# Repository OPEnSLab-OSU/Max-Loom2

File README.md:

# Max Documentation

## Purpose

* Designed to interface with the Loom Internet of Things Rapid Prototyping framework ([GitHub - OPEnSLab-OSU/Loom: Arduino library for Internet of Things Rapid Prototyping in environmental sensing](https://github.com/OPEnSLab-OSU/Loom))
* Uses software Max: [What is Max? | Cycling ’74](https://cycling74.com/products/max)
	* Tool for creating interactive software

### This Readme
* Designed to cover the usage of Max for interfacing with Loom, as well as some details of how it is implemented
	* It is not designed to be a readme of how to modify / create new patches or functionality

### Where to Put these Files
* Place this folder into the following directory:
  * If using Max 7 or 8:
    * [user] / Documents / Max 7 / Library
  * If using Max 6:
    * [user] / Applications / Max6 / Cycling74 

*Note: most of these the Max Loom files are developed in Max 8, functionality outside of this version may vary*

### Developer notes:
* These files should be in the same folder
* Some functionality (e.g. UDP communication) will only work on Max 8
* The Z_ patches may not work or depend on non-default features in Max 8

- - - -

# Installation Guide
## Download Max:
Go to Cycling 74 and download the version for your operating system.

Open Max 8 Application so the support folders you need to place the support files generate in your Documents folder.

You may want to create an account for authorization

## Download Loom Tools for Max:
* Go to: [https://github.com/OPEnSLab-OSU/Max-Loom2](https://github.com/OPEnSLab-OSU/Max-Loom2)
* Click the green button on the right to download the .zip of the repo.
* Unzip

Find these three folders:
* Loom2
* MPG
* Optron

Drag these folders into the following folder on your computer: 

(User) > Documents > Max 8 > Library 

## Download Java:
Make sure java is installed, especially if you are a windows user. 

Install Java here. [Java](https://www.java.com/en/download/manual.jsp)

## Download Java Virtual Machine (JDK):
Even if you installed Java above, you still need to do the following:
In a google search, type in: "download oracle java"
Click Java SE Downloads
Look for Oracle JDK and click the JDK download link 
Choose the operating system that matches your computer and download.
[Direct Link](https://www.oracle.com/java/technologies/javase-jdk14-downloads.html)

## Download the FTDI VCP drivers (virtual com port)
[ftdichip.com/drivers/vcp.htm](ftdichip.com/drivers/vcp.htm)

Don't download the D2xx drivers.
You only need to download the VCP drivers.
(make sure to download the executable version for your opperating system)

## Download Link Tools:
* From the Max 8 application, look for the menu item > Package manager
* Top right corner, type “link” in the search bar
* Install Link by Cycling ‘74

## reStart and reOpen Max 8:
* Quit Max, you may need to restart your computer too.
* Reopen Max8

## Try Things Out:
On your computer, Open (User) > Documents > Max 8 > Library > Loom2 > _DataProcessor.MPG.maxpat

- - - -

# Patches

* Patches are self-contained blocks with inputs and outputs for commands / data
* Inlets are the little circles at the top of a patch, hovering over them will give a description
* Outlets are the little circles at the bottom of a patch, hovering over them will give a description

## General

#### ModuleCore (primary input from Loom device)
##### Description

* Can think of as a representation a Loom device (device running Loom software, and enabled with Max interfacing features)
* A number of the patches are intended to be parallels to individual features / components enabled in the config of the Loom device

##### UI Elements

* `Instance number`: Enter the device number to connect to (specified in the config file)
* `Data updating`: When data is being received, this indicator blinks when data is being received (updates at 500ms interval if data is being received faster than that)
* `Battery indicator`: Display the battery level of the connected Loom device
* `Device name`: The name of the Loom device as specified in the config file
* `Send IP button`: Press to send the IP of the computer running Max to the Loom device. The device will save this and send data to specifically that IP rather than broadcasting data (increases data reliability)

##### Inlets

1. `Device ID In`: change the device to connect to
2. `JS Commands In`: Commands from actuator patches to converted to format and send to the Loom device
3. `Bang to Send IP`: Input bang signal to send IP to Loom device

##### Outlets

1. `Json Out`: Received data in Json format
2. `Data Dictionary Out`: Received data in Max dictionary format

- - - -

## Displays

### GeneralViewer
##### Description

* Accepts data as either a Json object or a Max Dictionary and displays is for easier viewing

##### UI Elements

* Large area to display data
* ‘Freeze’ button to prevent new data from overwriting currently displayed data

##### Inlets

1. `Data (Json) In`: Data in Json format (works with non-Loom data)
2. `Data (Dict) In`: Data in Max dictionary format (works with non-Loom data)

##### Outlets

1. None

### Sensor
##### Description

* Displays data from Loom devices 
* Intended to be connected to ’Json Out’ outlet of a ‘ModuleCore’

##### UI Elements

* Drop down of which sensor to display data for (items correspond to Loom Modules)
* Drop down of which element to display for the selected sensor / module
* Last reported value
* Moving average histogram of recent values

##### Inlets

1. `Data (Json) In`

##### Outlets

1. Outgoing data of current parameter 

##### Notes

* Data parsing and UI updating is primarily done via Sensor.js script

### PositionVisualizer
##### Description

* Displays the 3D orientation of Loom device with MPU6050
* Intended to be connected to ’Json Out’ or ‘Data Dictionary Out’ outlet of a ‘ModuleCore’

##### UI Elements

* Orientation visualization

##### Inlets

1. `Data (Json) In`: Loom data from ModuleCore
2. `Data (Dict) In`: Loom data from ModuleCore

##### Outlets

1. Output

- - - -

## Outputs (to network)

### Neopixel
##### Description

* Set the color of a Neopixel connected to a Loom device (generally connected to an Ishield)
* Corresponds to Loom ‘Neopixel’ module

##### UI Elements

* ‘Send’ button: generate command
* Dropdown menu to select which port the Neopixel / Neopixel chain is connected to 
* Dropdown menu to select which Neopixel to set in an a chain
* Sliders to select red, green, and blue values (0-255)

##### Inlets

1. `Bang to Send`: generate command upon bang 
2. `Reset to Defaults`
3. `Port Number`
4. `Neopixel # In Chain`
5. `Red Value (0-255)`
6. `Green Value (0-255)`
7. `Blue Value (0-255)`

##### Outlets

1. `JS Command Out`: Intended to be connected ‘JS Commands In’ outlet of ‘ModuleCore’

### Relay
##### Description

* Set the state of a relay connected to a Loom device
* Corresponds to Loom `Relay` module

##### UI Elements

* ‘Send’ button: generate command
* Button toggle to set relay state (green: enabled, gray: off)
* ‘Auto Send’ toggle: (enabled: changing main toggle immediately generates command: disabled: commands only generated when ‘Send’ button is pressed

##### Inlets

1. `Bang to Send`: generate command upon bang 
2. `Set State (1 on, 0 off)`

##### Outlets

1. `JS Command Out`: Intended to be connected ‘JS Commands In’ outlet of ‘ModuleCore’

### Servo
##### Description

* Set the position of a servo connected to a Loom device
* Corresponds to Loom ‘Servo’ module

##### UI Elements

* ‘Send’ button: generate command
* Dropdown to select which servo to set

##### Inlets

1. `Bang to Send`: generate command upon bang 
2. `Reset to Defaults`
3. `Servo Number` 
4. `Degree`

##### Outlets

1. `JS Command Out`: Intended to be connected ‘JS Commands In’ outlet of ‘ModuleCore’

### Stepper
##### Description

* Control rotation of stepper connect to Loom device
* Corresponds to Loom ‘Servo’ module

##### UI Elements

* ‘Send’ button: generate command
* Dropdown to select which motor to control
* Number of steps to move input 
* Speed entry: 10-250

##### Inlets

1. `Bang to Send`: generate command upon bang 
2. `Reset to Defaults` 
3. `Motor #`
4. `Set Speed`
5. `Clockwise`

##### Outlets

1. `JS Command Out`: Intended to be connected ‘JS Commands In’ outlet of ‘ModuleCore’

### SetInterval
##### Description

* Set the refresh rate of a Loom device

##### UI Elements

* ‘Send’ button: generate command

##### Inlets

1. `Bang to Send`: generate command upon bang 
2. `Interval (ms)`: refresh rate of Loom devices

##### Outlets

1. `JS Command Out`: Intended to be connected ‘JS Commands In’ outlet of ‘ModuleCore’

#### SelectSD_Config
##### Description

* Specify a config file for a Loom device to reinitialize with
* Requires that the Loom device be connected to an SD card

##### UI Elements

* Dropdown to select Loom config file (names populated from items in ‘SD_Json_Menu.txt’
  * Populate .txt file with common config names
* Text box to manually enter Loom config file name

##### Inlets

1. `Bang to Send`: generate command upon bang 
2. `Reset to Defaults`

##### Outlets

1. `JS Command Out`: Intended to be connected ‘JS Commands In’ outlet of ‘ModuleCore’

- - - -

## Middleware Patches 
*Used for transforming values / data streams*

### Aux_RangeSetter
##### Description
  * Scales an input stream of values to fit within the specified ‘Min’ and ‘Max’ values
  * Intended that the ‘Learn’ toggle be active while adjusting the input (output from a Loom device or otherwise) between its maximum ranges, then deactivating ‘Learn’
    * Subsequent values will use the detected min and max values of the input and map them to the output min and max values, with other values being interpolated within the range
    * Incoming values outside of the learned min and max while ‘Learn’ is disabled will be capped within the range
  * Rescales an incoming data stream of an unknown range into a stream with a specified minimum and maximum range. Range Setter automatically adjusts and compares incoming values based on the least and greatest values it received while in "Learn" mode. 

##### UI Elements
  * Output ‘Min’ and ‘Max’ range
* ‘Learn’ toggle: enable and send your min and max value. Then disable to save min/max and disable Learn mode.
* Mapped value of most recent input value
* History of values
* Reset button: Clear learned ranged
##### Inlets
1. `Incoming Values`: stream of values to remap
2. `Save/reset`: 1: reset learned values and enable learn mode, 0: disable learn mode, saving learned range
##### Outlets
1. `Range adjusted value`: stream of values remapped to specified range

### Aux_ScaleCurve
##### Description
  * Remap a [0, 1] data stream through a selection of functions
  * Data not in [0, 1] can be remapped to this range with ‘Rescale’ or ‘Range Setter’ patches
  * Transformation equations:
    * x is in range [0, 1] 
    * Cosine: (x–1^3) * (x+1^3) + 1
    * CrossFadeIn: sin(x * π/2)
    * Exponential: x^a
    * Linear: Simply caps input stream to [0,1) range
    * Bell: sin(x * π)
    * Gaussian: e^[–(x–0.5^2) / (2*(0.157^2)]
    * InvGauss: -e^[–(x–0.5^2) / (2*(0.157^2)] + 1
    * Inverted Ramp: cos(x * π) 
##### UI Elements
  * Dropdown to select which function to map input stream to
  * Exponent: Only applies if ‘exponential’ function is selected
  * Visualization of function and current input and output values along the curve
  * Histogram of recent values
##### Inlets
  1. `Value to Scale`: Stream of data (or single value), representing ‘x’ values to specified functions (should be in [0,1])
##### Outlets
  1. `Scaled Value`: Stream of data mapped through the specified equation

### Aux_ScaleLinear
##### Description
  * Maps a stream of data from the specified input range to the specified output range, interpolating to scale values
  * Similar to ‘Range Setter’ patch but expects know input range
##### UI Elements
  * Input Min and Max values
  * Output Min and Max values
##### Inlets
  1. `Value to Scale`: Input stream of data (or single value) to scale to a different range
##### Outlets
  1. `Scaled Value`: Stream of data remapped to specified range

### Aux_Smooth
##### Description
  * Smooths data stream logarithmically
  * Uses an averaging function to affect rising and falling in a data stream. This can have a smoothing affect on the data stream,
  * Slider values indicate how many samples to average together
  * Also note, The Smooth value is inversely correlational to the data's responsiveness. i.e. the higher the Smoothing value, the more sluggish the data will be to respond in a rising or falling direction
##### UI Elements
  * Filter strength rising: [0,21], strength of smoothing on rising data
  * Filter strength falling: [0,21], strength of smoothing on falling data
  * Histogram of recent values:
  * Most recent value
##### Inlets
  1. `Value to Smooth`: Stream of data to smooth
##### Outlets
  1. `Smoothed Value`: Stream of data smoothed 

### Aux_Threshold
##### Description
  * Output boolean values triggered when a stream of data values risings or falls past specified thresholds
##### UI Elements
  * Rising threshold: If previous value is <= this value and most recent value is >, output true
  * Falling threshold: If previous value is >= this value and most recent value is <, output false
  * Invert logic toggle: Invert the boolean output
##### Inlets
  1. Data stream to check threshold on
  2. Rising threshold: Value to use as rising threshold
  3. Falling threshold: Value to use as falling threshold
##### Outlets
  1. True of false based on logic 

### Aux_pH
##### Description
  * Used to convert raw millivolt readings of a pH probe to a pH value
  * Calibrate the sensor by getting the readings in buffers with pH of 4 and 7
##### UI Elements
  * Acid pH 4 calibration reading: millivolt reading when probe is placed in buffer with pH 4
  * Neutral pH 7 calibration reading:  millivolt reading when probe is placed in buffer with pH 7
  * Calculated pH of current mV reading
##### Inlets
  1. Current reading in (mV)
  2. pH 4 Acid mV
  3. pH 7 Neutral mV
##### Outlets
  1. pH value 

- - - -

## Other
Additional patches created before the current design of Loom. Support with Loom functionality may vary

* Z_3Dpan
* Z_App3DPan
* Z_AppVST
* Z_ArduinoIn
* Z_ChordDegree
* Z_Concatenate
* Z_DMX
* Z_Draw
* Z_DrumKit
* Z_Follower_GUI
* Z_InstrumentPosition
* Z_MidiIn
* Z_MidiOut
* Z_Movement
* Z_Musicbox
* Z_OSC_In
* Z_OSC_Out
* Z_OutLightsaber
* Z_RotaryDial
* Z_ScaleDegree
* Z_Sequencer
* Z_SimpleSamp
* Z_Spring
* Z_Switchblade
* Z_TapTempo

- - - -

## Data Processor
* Essentially a sandbox to use the other patches
* Starts out with just the ‘Patch Generator’
  * Has a dropdown of ‘patches’ that can be generated
    * Sorted in terms of inputs, outputs, data modification,  visualization
  * ‘Clear Last Patch’: deletes the most recently generated patch
  * ‘Clear All Patches’: deletes all patches 
  * Relevant files:
    * Patch_Generator.maxpat
    * PatchList.txt (kept separate so it is easy to modify list as new patches are added

### Usage
* Generate patches 
* Designed primarily to be used with Loom devices, so generating a/multiple ModuleCores will be useful
  * Once the device number is set to match the corresponding Loom device (number set in the Loom config file), data will output from the to outlets of the patch
* Attach viewers / data processing patches to the outlets 
* Attach command generating patches to inlets

* If you need to modify / inspect the internals of the patch that was generated in a DataProcessor file, you can Right Click > Object > ‘New View of Embedded Patcher’ (or ‘New Patcher with Contents of Embedded Patcher’ if you don’t want modifications to affect the DataProcessor file

* Can ‘Save As’ to create templated

- - - -

## Loom Implementation

### MaxSub
* Receives commands from Max
  * Commands can be generated from actuator patches connected to a ‘ModuleCore’ (or can be manually created strings)
* Can be run without MaxPub if you only want to receive commands and not send data, reliability may not be as good as with both modules
* Commands will be routed to ‘MaxSub’ module, which will ‘dispatch’ the command to the corresponding module’s ‘dispatch’ method to act upon it
* Needs `Loom.MaxSub().subscribe();` in the main loop
* Receives on UDP port 9000 + instance number (thus Max sends on this port)
* Requires an ‘InternetPlat’ module be instantiated
* When ‘ModuleCore’ is created / ‘Send IP’ is pressed, Max sends out the IP of the computer it is running on to the device of the specified instance number, if such a devices exists and is running ‘MaxSub’ and ‘MaxPub’ modules, the device will set that IP in the ‘MaxPub’ module to have better reliability sending messages 

### MaxPub
* Used to send data out to Max
* Can be used without MaxSub if you only want to send data, reliability may not be as good as with both modules
* Sends on UDP port 8000 + instance number (thus Max receives on this port)
* Requires an ‘InternetPlat’ module be instantiated
* Needs `Loom.MaxPub().publish();` in the main loop
  * After measuring and packaging data, this will send the data object/package out to Max

- - - -

## Max Implementation

### Loom Core
* Represents a Loom devices 
  * Outputs Loom device packaged data
  * Inputs commands to send to Loom device
* Nearly all of the logic is controlled by `Controller.js` file (the rest is essentially just the UI elements and formatting inputs to send to the Javascript object)

#### Controller.js Functions
* `json(j)`
  * Parse data the has been received via UDP in the `UDP_In` patcher (which does some initial preprocessing / filtering of non-data; see `Convert_Incoming.js` for details)
  * Calls function to update UI with new data
  * Extract the IP address of the Loom device, and respond with command to MaxPub module to have Loom device set the remote IP to be the IP of the computer running Max
  * Update the `Data` dict object
  * Forward the data json out
* `update_UI()`
  * Calls functions to update UI elements for battery, device name, blink messages received
* `update_UI_battery()`
  * Update the battery UI element (named `battery_indicator`) with the last received battery voltage
* `update_UI_device_name()`
  * Update the device name UI element (named `device_name`) with last received device name 
  * Max only specifies the device to connect to by ID number, it does not know about the name until it receives data, which is displayed for better human readability
* `update_UI_blink_received()`
  * Update the UI LED that blinks when data is received
* `enable_log(e)`
  * Enable or disable logging to the Max console
* `set_instance(i)`
  * Reset the UI of current device info
  * Set the UDP elements to receive / send on the updated ports
* `command(argSymbol)`
  * Given a symbol (string) of a command, format a message that the MaxSub module will recognize and be able to dispatch
  * Send the json command out to `UDP_Out` to be sent over UDP
* `reset_UI()`
  * Any UI clearing / resetting that needs to happen when switching devices, for example
* `set_ip()`
  * Create a command to MaxPub module to have Loom device set the remote IP to be the IP of the computer running Max
  * Send the json command out to `UDP_Out` to be sent over UDP

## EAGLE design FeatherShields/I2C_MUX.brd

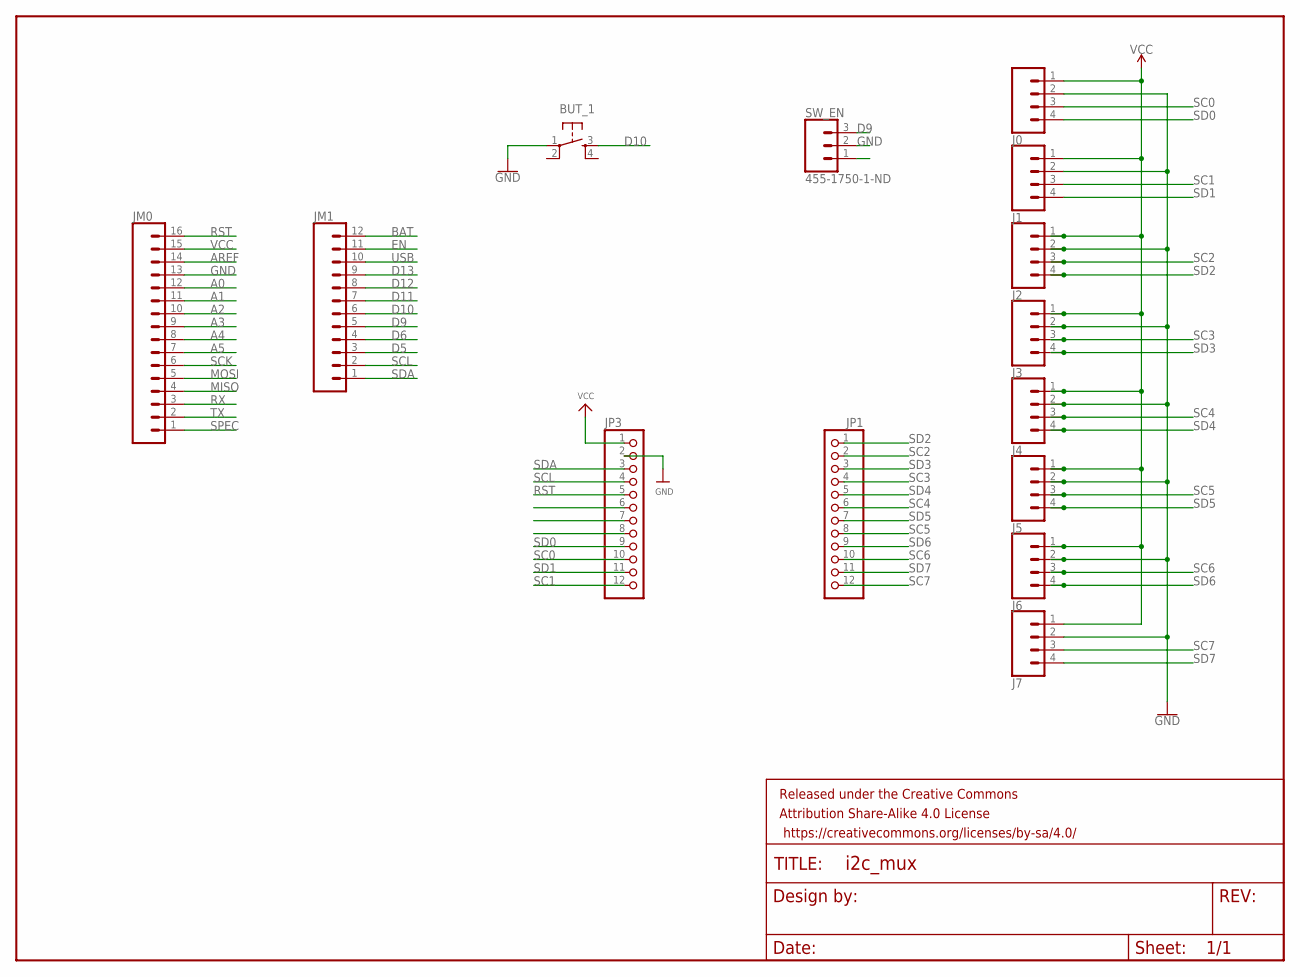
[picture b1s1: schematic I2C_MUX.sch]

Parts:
BUT_1: TAC_SWITCHPTH; TACTILE-PTH
FRAME1: FRAME-LETTER; CREATIVE_COMMONS
J0, J1, J2, J3, J4, J5, J6, J7: CONN_04POLAR; MOLEX-1X4
JM0: CONN_16; 1X16
JM1: CONN_12; 1X12
JP1, JP3: HEADER-1X12; 1X12_ROUND
SW_EN: 455-1750-1-ND; 1X03

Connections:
A0: JM0.12
A1: JM0.11
A2: JM0.10
A3: JM0.9
A4: JM0.8
A5: JM0.7
AREF: JM0.14
BAT: JM1.12
D5: JM1.3
D6: JM1.4
D9: JM1.5, SW_EN.3
D10: BUT_1.3, JM1.6
D11: JM1.7
D12: JM1.8
D13: JM1.9
EN: JM1.11
GND: BUT_1.1, J0.2, J1.2, J2.2, J3.2, J4.2, J5.2, J6.2, J7.2, JM0.13, JP3.2, SW_EN.2
MISO: JM0.4
MOSI: JM0.5
RST: JM0.16, JP3.5
RX: JM0.3
SC0: J0.3, JP3.10
SC1: J1.3, JP3.12
SC2: J2.3, JP1.2
SC3: J3.3, JP1.4
SC4: J4.3, JP1.6
SC5: J5.3, JP1.8
SC6: J6.3, JP1.10
SC7: J7.3, JP1.12
SCK: JM0.6
SCL: JM1.2, JP3.4
SD0: J0.4, JP3.9
SD1: J1.4, JP3.11
SD2: J2.4, JP1.1
SD3: J3.4, JP1.3
SD4: J4.4, JP1.5
SD5: J5.4, JP1.7
SD6: J6.4, JP1.9
SD7: J7.4, JP1.11
SDA: JM1.1, JP3.3
SPEC: JM0.1
TX: JM0.2
USB: JM1.10
VCC: J0.1, J1.1, J2.1, J3.1, J4.1, J5.1, J6.1, J7.1, JM0.15, JP3.1

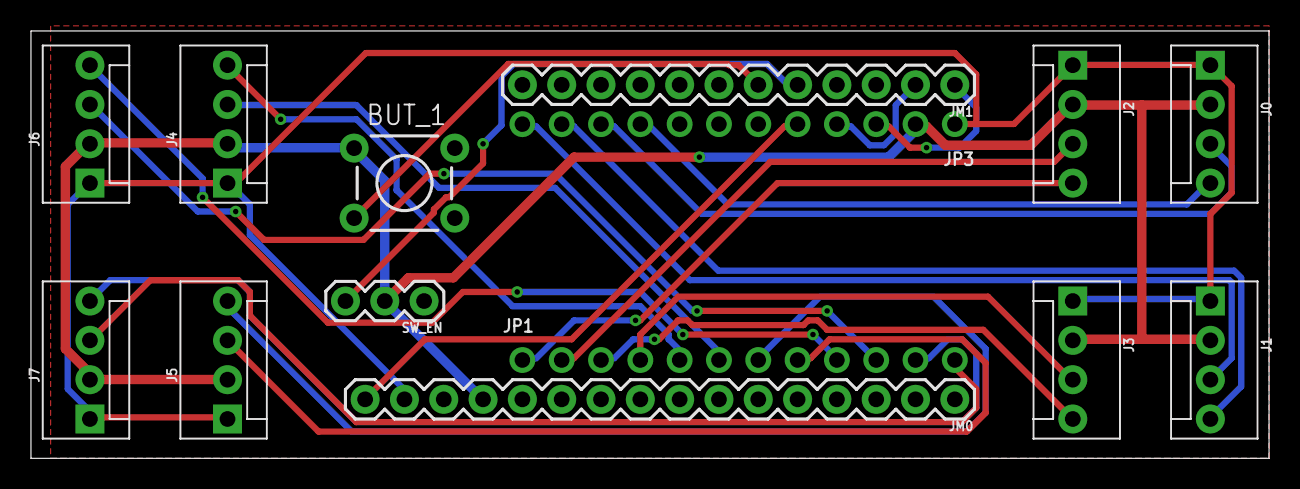
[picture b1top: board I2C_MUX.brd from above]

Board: 2 copper layers, 80.0 x 27.6 mm, 15 parts (0 on the bottom side), 23 nets.

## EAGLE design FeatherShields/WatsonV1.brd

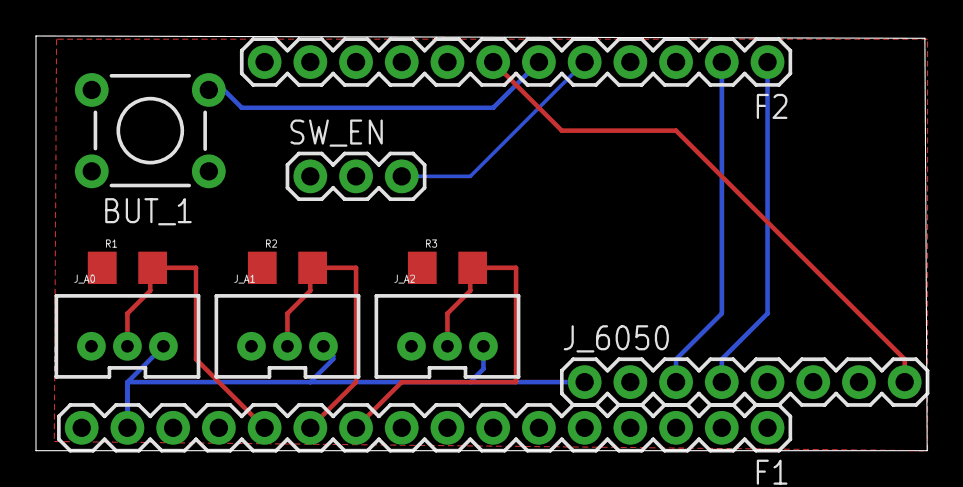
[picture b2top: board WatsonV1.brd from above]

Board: 2 copper layers, 49.5 x 23.0 mm, 11 parts (0 on the bottom side), 10 nets.

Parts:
BUT_1: TACTILE-PTH
F1: 1X16
F2: 1X12
J_6050: 1X08_ROUND
J_A0, J_A1, J_A2: JST-3-PTH-VERT
R1, R2, R3: 30k 63mW; 1206
SW_EN: 1X03

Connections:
A0: F1.12, J_A0.2, R1.2
A1: F1.11, J_A1.2, R2.2
A2: F1.10, J_A2.2, R3.2
BUTT: BUT_1.3, F2.6
GND: BUT_1.1, F1.13, J_6050.2, J_A0.1, J_A1.1, J_A2.1, R1.1, R2.1, R3.1, SW_EN.2
MPU_INT: F2.7, J_6050.8
SCL: F2.2, J_6050.3
SDA: F2.1, J_6050.4
SW: F2.5, SW_EN.3
VCC: F1.15, J_6050.1, J_A0.3, J_A1.3, J_A2.3

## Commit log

2019-08-09 Add new Loom 2 compliant Max patches
2019-08-13 Post demo improvements
2019-08-21 Add gitignore
2019-08-21 Update Max patches
2019-09-04 Add old max patches back
2019-09-17 Sensor param selection saved
2019-09-23 Add back some of the old patches
2020-09-16 update All
2020-09-22 watson board added
2020-09-22 i2cMux and Decagon shields
2020-09-28 Fixed airwire
2020-09-30 Add readme
2020-09-30 Fix readme formatting
2020-11-07 Updates to support Loom WiFi access point mode
2020-12-01 upload ICST
2020-12-11 Update All Emulator Fix
2021-03-01 Improve reliability of 'Send IP' command

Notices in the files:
parts and their libraries:
SparkFun-Retired: Licensing: Creative Commons ShareAlike 4.0 International - https://creativecommons.org/licenses/by-sa/4.0
SparkFun-Aesthetics: Released under the Creative Commons Attribution Share-Alike 4.0 License
SparkFun-Aesthetics: https://creativecommons.org/licenses/by-sa/4.0
